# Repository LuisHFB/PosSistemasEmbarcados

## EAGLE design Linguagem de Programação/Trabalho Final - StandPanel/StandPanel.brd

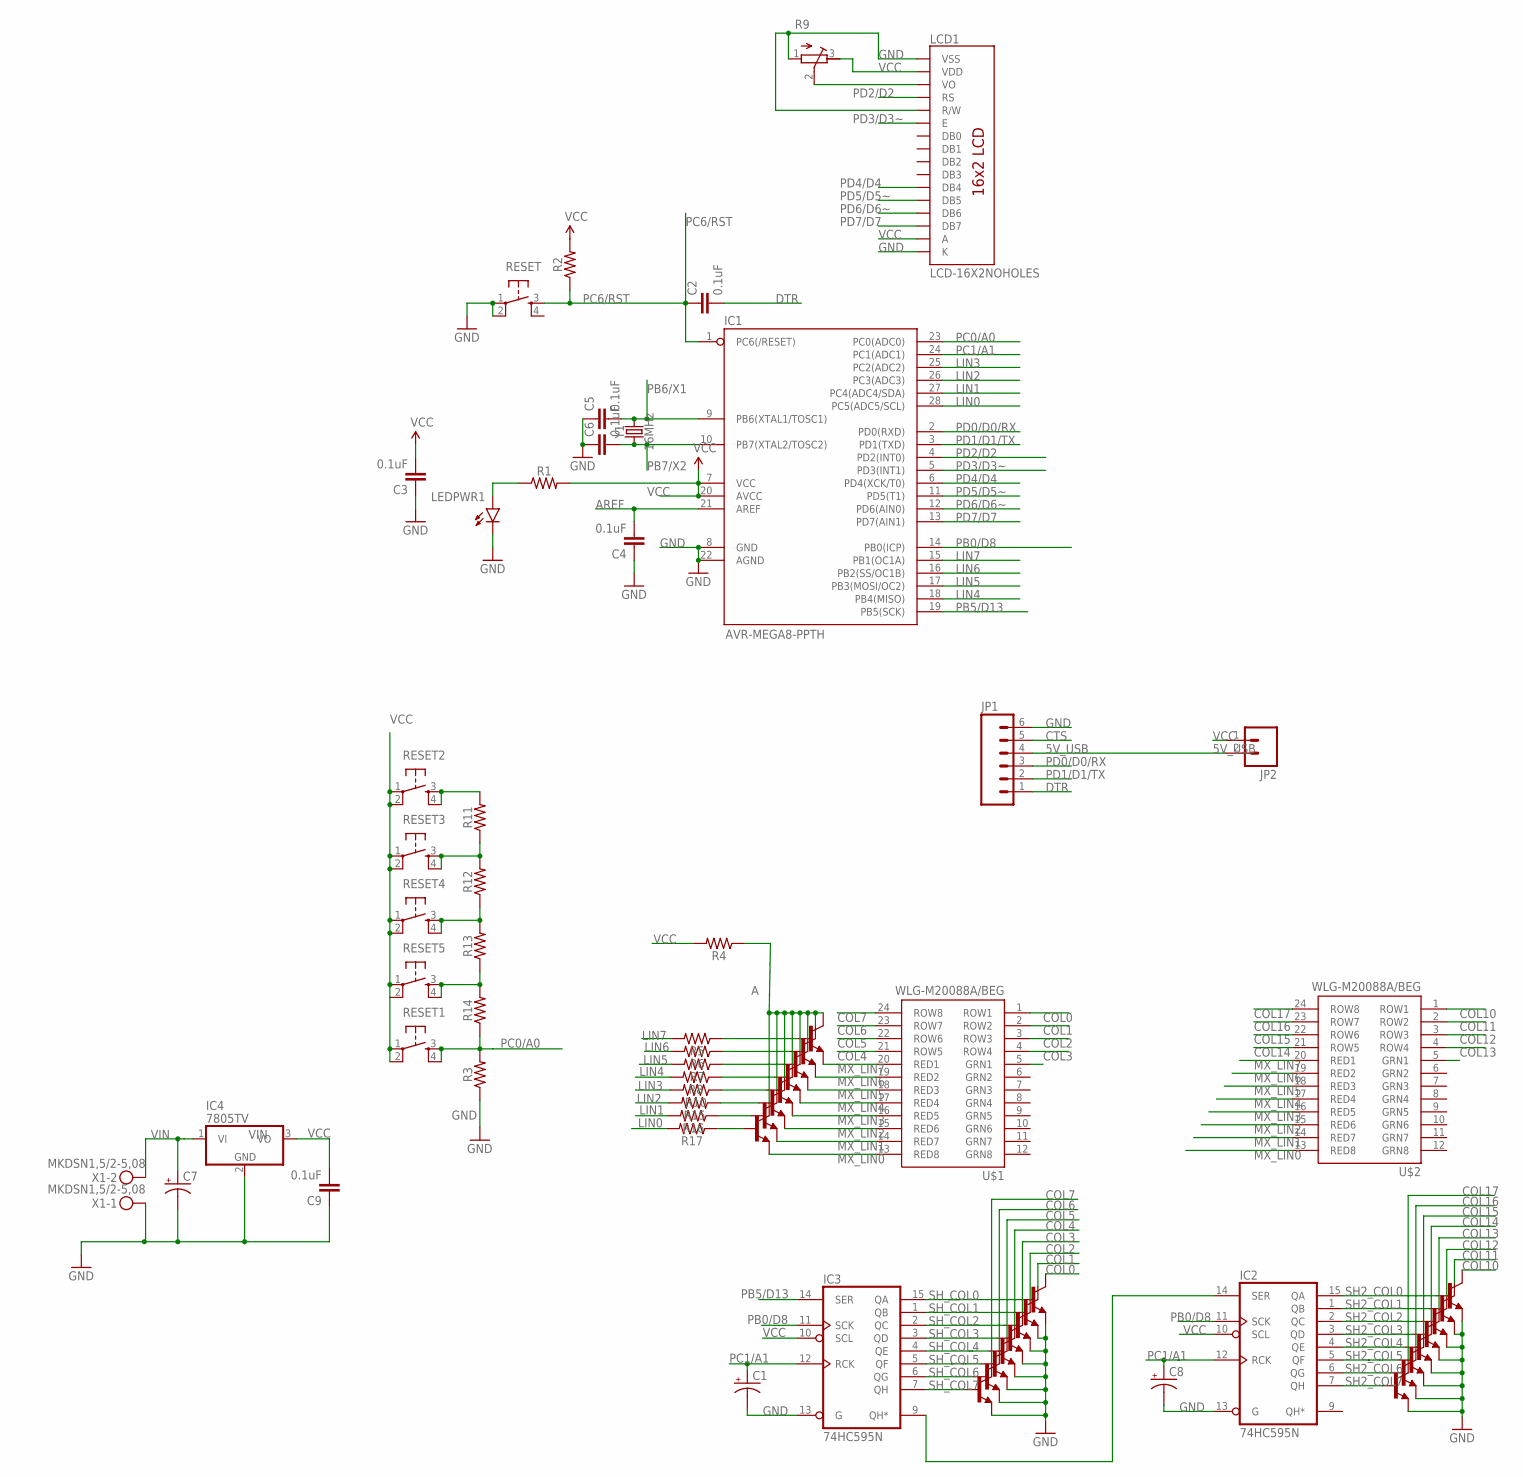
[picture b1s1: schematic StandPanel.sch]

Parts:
C1, C8: CAP_POLPTH2; CPOL-RADIAL-10UF-25V
C2, C3, C4, C5, C6, C9: 0.1uF; CAP-PTH-SMALL-KIT
C7: CAP_POLPTH1; CPOL-RADIAL-100UF-25V
IC1: AVR-MEGA8-PPTH; DIL28-3
IC2, IC3: 74HC595N; DIL16
IC4: 7805TV; TO220V
JP1: M06SIP; 1X06
JP2: M02PTH; 1X02
LCD1: LCD-16X2NOHOLES; LCD-16X2_NOHOLESNOSILK
LEDPWR1: LED5MM-KIT; LED_5MM-KIT
R1, R2, R3, R4, R5, R6, R7, R8, R10, R11, R12, R13, R14, R15, R16, R17: AXIAL-0.3-KIT
R9: R-TRIMM3296W; RTRIM3296W
RESET, RESET1, RESET2, RESET3, RESET4, RESET5: TAC_SWITCHPTH; TACTILE-PTH
T1, T3, T4, T5, T6, T7, T8, T9, T10, T11, T12, T13, T14, T15, T16, T17, T25, T26, T27, T28, T29, T30, T31, T32: BC337; TO92
U$1, U$2: WLG-M20088A/BEG; WLG-M2088A/8EG
X1: MKDSN1,5/2-5,08
Y1: 16MHz; HC49US

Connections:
5V_USB: JP1.4, JP2.2
A: R4.P$1 (1), T1.3 (C), T3.3 (C), T4.3 (C), T5.3 (C), T6.3 (C), T7.3 (C), T8.3 (C), T9.3 (C)
AREF: C4.2, IC1.21 (AREF)
COL0: T10.3 (C), U$1.1 (ROW1)
COL1: T11.3 (C), U$1.2 (ROW2)
COL2: T12.3 (C), U$1.3 (ROW3)
COL3: T13.3 (C), U$1.4 (ROW4)
COL4: T14.3 (C), U$1.21 (ROW5)
COL5: T15.3 (C), U$1.22 (ROW6)
COL6: T16.3 (C), U$1.23 (ROW7)
COL7: T17.3 (C), U$1.24 (ROW8)
COL10: T25.3 (C), U$2.1 (ROW1)
COL11: T26.3 (C), U$2.2 (ROW2)
COL12: T27.3 (C), U$2.3 (ROW3)
COL13: T28.3 (C), U$2.4 (ROW4)
COL14: T29.3 (C), U$2.21 (ROW5)
COL15: T30.3 (C), U$2.22 (ROW6)
COL16: T31.3 (C), U$2.23 (ROW7)
COL17: T32.3 (C), U$2.24 (ROW8)
CTS: JP1.5
DTR: C2.2, JP1.1
GND: C1.2 (-), C3.1, C4.1, C5.1, C6.1, C7.2 (-), C8.2 (-), C9.1, IC1.8 (GND), IC1.22 (AGND), IC2.8 (GND), IC2.13 (G), IC3.8 (GND), IC3.13 (G), IC4.2 (GND), JP1.6, LCD1.1 (VSS), LCD1.5 (R/W), LCD1.16 (K), LEDPWR1.K (C), R3.P$1 (1), R9.1 (A), RESET.1, RESET.2, T10.1 (E), T11.1 (E), T12.1 (E), T13.1 (E), T14.1 (E), T15.1 (E), T16.1 (E), T17.1 (E), T25.1 (E), T26.1 (E), T27.1 (E), T28.1 (E), T29.1 (E), T30.1 (E), T31.1 (E), T32.1 (E), X1.1
LIN0: IC1.28 (PC5(ADC5/SCL)), R17.P$2 (2)
LIN1: IC1.27 (PC4(ADC4/SDA)), R16.P$2 (2)
LIN2: IC1.26 (PC3(ADC3)), R15.P$2 (2)
LIN3: IC1.25 (PC2(ADC2)), R10.P$2 (2)
LIN4: IC1.18 (PB4(MISO)), R8.P$2 (2)
LIN5: IC1.17 (PB3(MOSI/OC2)), R7.P$2 (2)
LIN6: IC1.16 (PB2(SS/OC1B)), R6.P$2 (2)
LIN7: IC1.15 (PB1(OC1A)), R5.P$2 (2)
LIN8: T10.2 (B)
MX_LIN0: T9.1 (E), U$1.13 (RED8), U$2.13 (RED8)
MX_LIN1: T8.1 (E), U$1.14 (RED7), U$2.14 (RED7)
MX_LIN2: T7.1 (E), U$1.15 (RED6), U$2.15 (RED6)
MX_LIN3: T6.1 (E), U$1.16 (RED5), U$2.16 (RED5)
MX_LIN4: T5.1 (E), U$1.17 (RED4), U$2.17 (RED4)
MX_LIN5: T4.1 (E), U$1.18 (RED3), U$2.18 (RED3)
MX_LIN6: T3.1 (E), U$1.19 (RED2), U$2.19 (RED2)
MX_LIN7: T1.1 (E), U$1.20 (RED1), U$2.20 (RED1)
unnamed: LEDPWR1.A, R1.P$1 (1)
unnamed: R17.P$1 (1), T9.2 (B)
unnamed: R16.P$1 (1), T8.2 (B)
unnamed: LCD1.3 (VO), R9.2 (S)
unnamed: R15.P$1 (1), T7.2 (B)
unnamed: IC2.14 (SER), IC3.9 (QH*)
unnamed: R10.P$1 (1), T6.2 (B)
unnamed: R8.P$1 (1), T5.2 (B)
unnamed: R7.P$1 (1), T4.2 (B)
unnamed: R6.P$1 (1), T3.2 (B)
unnamed: R5.P$1 (1), T1.2 (B)
unnamed: R11.P$2 (2), RESET2.3, RESET2.4
unnamed: R11.P$1 (1), R12.P$2 (2), RESET3.3, RESET3.4
unnamed: R12.P$1 (1), R13.P$2 (2), RESET4.3, RESET4.4
PB0/D8: IC1.14 (PB0(ICP)), IC2.11 (SCK), IC3.11 (SCK)
PB5/D13: IC1.19 (PB5(SCK)), IC3.14 (SER)
PB6/X1: C5.2, IC1.9 (PB6(XTAL1/TOSC1)), Y1.2
PB7/X2: C6.2, IC1.10 (PB7(XTAL2/TOSC2)), Y1.1
PC0/A0: IC1.23 (PC0(ADC0)), R3.P$2 (2), R13.P$1 (1), R14.P$1 (1), R14.P$2 (2), RESET1.3, RESET1.4, RESET5.3, RESET5.4
PC1/A1: C1.1 (+), C8.1 (+), IC1.24 (PC1(ADC1)), IC2.12 (RCK), IC3.12 (RCK)
PC6/RST: C2.1, IC1.1 (PC6(/RESET)), R2.P$1 (1), RESET.3
PD0/D0/RX: IC1.2 (PD0(RXD)), JP1.3
PD1/D1/TX: IC1.3 (PD1(TXD)), JP1.2
PD2/D2: IC1.4 (PD2(INT0)), LCD1.4 (RS)
PD3/D3~: IC1.5 (PD3(INT1)), LCD1.6 (E)
PD4/D4: IC1.6 (PD4(XCK/T0)), LCD1.11 (DB4)
PD5/D5~: IC1.11 (PD5(T1)), LCD1.12 (DB5)
PD6/D6~: IC1.12 (PD6(AIN0)), LCD1.13 (DB6)
PD7/D7: IC1.13 (PD7(AIN1)), LCD1.14 (DB7)
SH2_COL0: IC2.15 (QA), T25.2 (B)
SH2_COL1: IC2.1 (QB), T26.2 (B)
SH2_COL2: IC2.2 (QC), T27.2 (B)
SH2_COL3: IC2.3 (QD), T28.2 (B)
SH2_COL4: IC2.4 (QE), T29.2 (B)
SH2_COL5: IC2.5 (QF), T30.2 (B)
SH2_COL6: IC2.6 (QG), T31.2 (B)
SH2_COL7: IC2.7 (QH), T32.2 (B)
SH_COL0: IC3.15 (QA)
SH_COL1: IC3.1 (QB), T11.2 (B)
SH_COL2: IC3.2 (QC), T12.2 (B)
SH_COL3: IC3.3 (QD), T13.2 (B)
SH_COL4: IC3.4 (QE), T14.2 (B)
SH_COL5: IC3.5 (QF), T15.2 (B)
SH_COL6: IC3.6 (QG), T16.2 (B)
SH_COL7: IC3.7 (QH), T17.2 (B)
VCC: C3.2, C9.2, IC1.7 (VCC), IC1.20 (AVCC), IC2.10 (SCL), IC2.16 (VCC), IC3.10 (SCL), IC3.16 (VCC), IC4.3 (VO), JP2.1, LCD1.2 (VDD), LCD1.15 (A), R1.P$2 (2), R2.P$2 (2), R4.P$2 (2), R9.3 (E), RESET2.1, RESET2.2, RESET3.1, RESET3.2, RESET4.1, RESET4.2, RESET5.1, RESET5.2
VCC1: RESET1.1, RESET1.2
VIN: C7.1 (+), IC4.1 (VI), X1.2

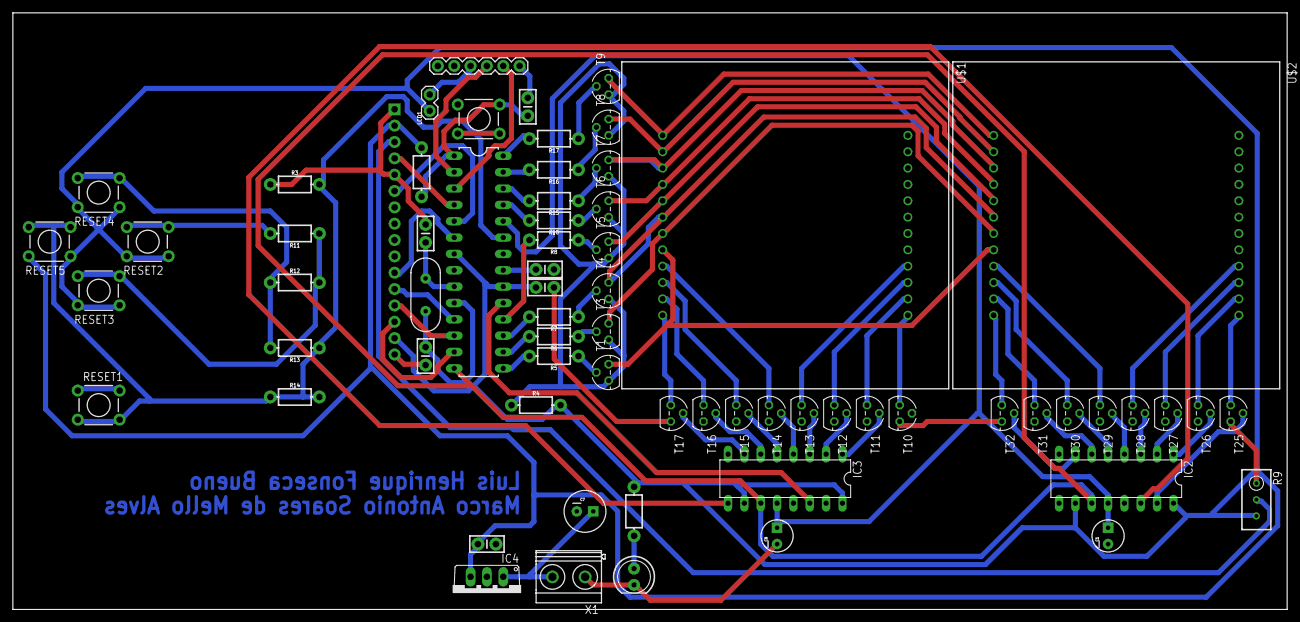
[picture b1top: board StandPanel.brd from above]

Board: 2 copper layers, 198.0 x 92.7 mm, 68 parts (0 on the bottom side), 84 nets.

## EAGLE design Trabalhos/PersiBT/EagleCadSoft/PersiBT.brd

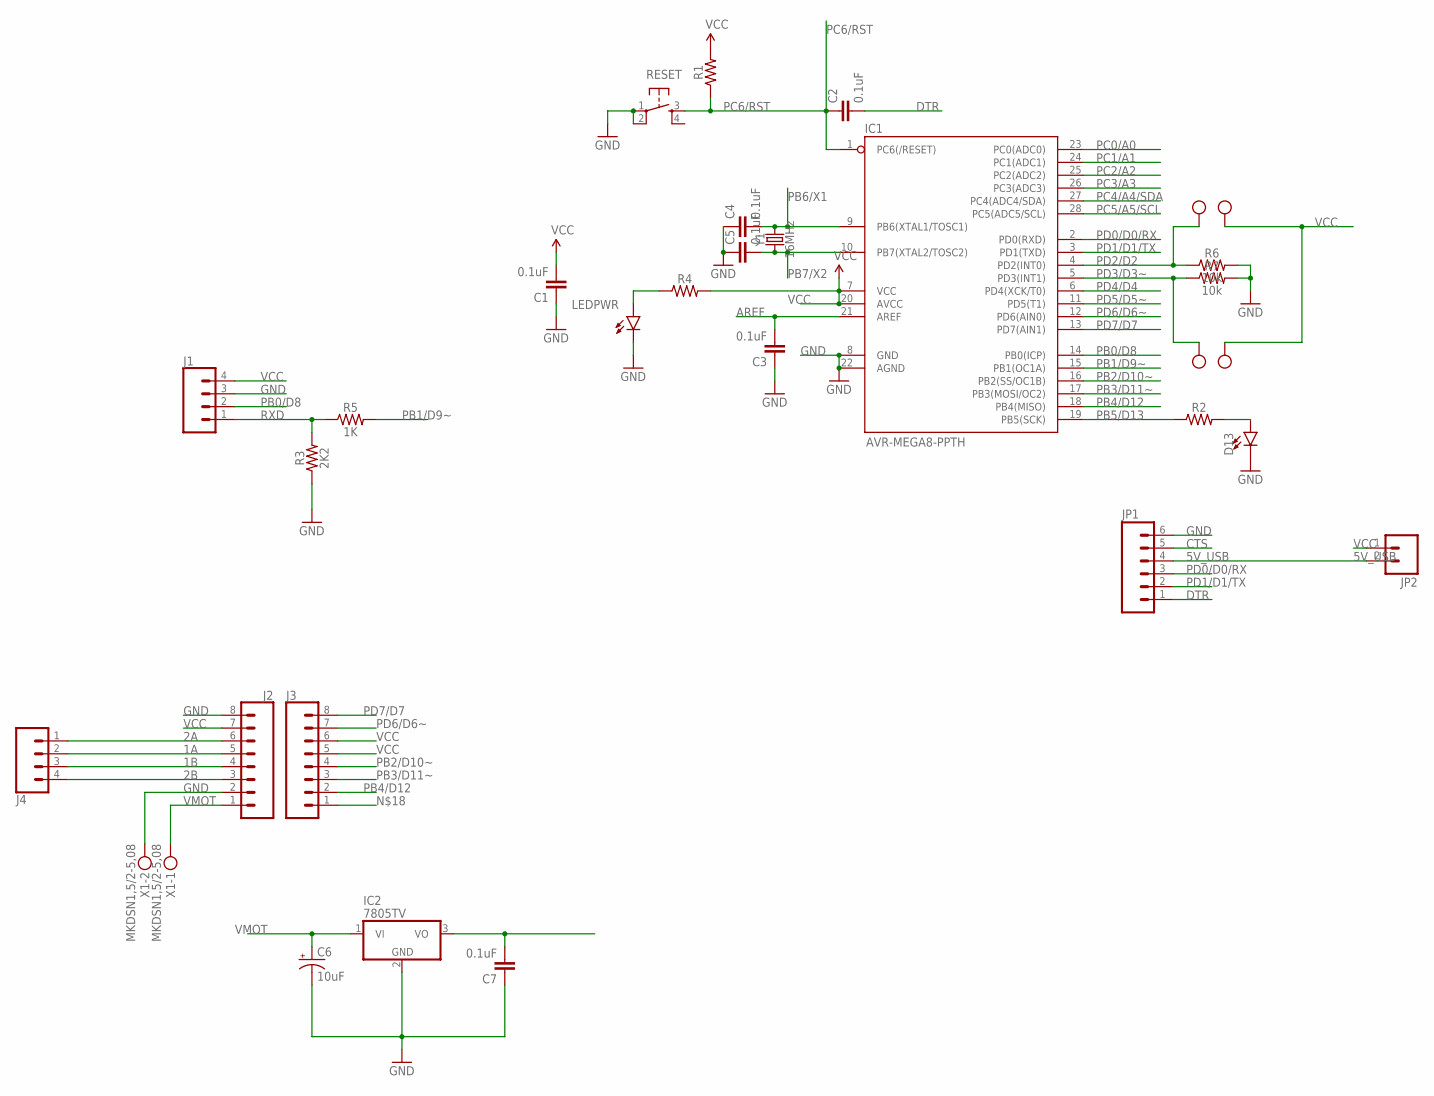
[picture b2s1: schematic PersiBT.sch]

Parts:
C1, C2, C3, C4, C5, C7: 0.1uF; CAP-PTH-SMALL-KIT
C6: 10uF; CPOL-RADIAL-2.5MM-5MM-KIT
D13: LED5MM-KIT; LED_5MM-KIT
IC1: AVR-MEGA8-PPTH; DIL28-3
IC2: 7805TV; TO220V
J1, J4: CONN_04; 1X04
J2, J3: CONN_08"; 1X08
JP1: M06SIP; 1X06
JP2: M02PTH; 1X02
LEDPWR: LED5MM-KIT; LED_5MM-KIT
R1, R2, R4: AXIAL-0.3-KIT
R3: 2K2; AXIAL-0.3-KIT
R5: 1K; AXIAL-0.3-KIT
R6, R7: 10k; AXIAL-0.3-KIT
RESET: TAC_SWITCHPTH; TACTILE-PTH
X1, X2, X3: MKDSN1,5/2-5,08
Y1: 16MHz; HC49US

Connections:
1A: J2.5, J4.2
1B: J2.4, J4.3
2A: J2.6, J4.1
2B: J2.3, J4.4
5V_USB: JP1.4, JP2.2
AREF: C3.2, IC1.21 (AREF)
CTS: JP1.5
DTR: C2.2, JP1.1
GND: C1.1, C3.1, C4.1, C5.1, C6.2 (-), C7.1, D13.K (C), IC1.8 (GND), IC1.22 (AGND), IC2.2 (GND), J1.3, J2.2, J2.8, JP1.6, LEDPWR.K (C), R3.P$1 (1), R6.P$2 (2), R7.P$2 (2), RESET.1, RESET.2, X1.2
unnamed: D13.A, R2.P$2 (2)
unnamed: LEDPWR.A, R4.P$1 (1)
PB0/D8: IC1.14 (PB0(ICP)), J1.2
PB1/D9~: IC1.15 (PB1(OC1A)), R5.P$2 (2)
PB2/D10~: IC1.16 (PB2(SS/OC1B)), J3.4
PB3/D11~: IC1.17 (PB3(MOSI/OC2)), J3.3
PB4/D12: IC1.18 (PB4(MISO)), J3.2
PB5/D13: IC1.19 (PB5(SCK)), R2.P$1 (1)
PB6/X1: C4.2, IC1.9 (PB6(XTAL1/TOSC1)), Y1.2
PB7/X2: C5.2, IC1.10 (PB7(XTAL2/TOSC2)), Y1.1
PC0/A0: IC1.23 (PC0(ADC0))
PC1/A1: IC1.24 (PC1(ADC1))
PC2/A2: IC1.25 (PC2(ADC2))
PC3/A3: IC1.26 (PC3(ADC3))
PC4/A4/SDA: IC1.27 (PC4(ADC4/SDA))
PC5/A5/SCL: IC1.28 (PC5(ADC5/SCL))
PC6/RST: C2.1, IC1.1 (PC6(/RESET)), R1.P$1 (1), RESET.3
PD0/D0/RX: IC1.2 (PD0(RXD)), JP1.3
PD1/D1/TX: IC1.3 (PD1(TXD)), JP1.2
PD2/D2: IC1.4 (PD2(INT0)), R6.P$1 (1), X2.1
PD3/D3~: IC1.5 (PD3(INT1)), R7.P$1 (1), X3.2
PD4/D4: IC1.6 (PD4(XCK/T0))
PD5/D5~: IC1.11 (PD5(T1))
PD6/D6~: IC1.12 (PD6(AIN0)), J3.7
PD7/D7: IC1.13 (PD7(AIN1)), J3.8
RXD: J1.1, R3.P$2 (2), R5.P$1 (1)
VCC: C1.2, C7.2, IC1.7 (VCC), IC1.20 (AVCC), IC2.3 (VO), J1.4, J2.7, J3.5, J3.6, JP2.1, R1.P$2 (2), R4.P$2 (2), X2.2, X3.1
VMOT: C6.1 (+), IC2.1 (VI), J2.1, X1.1

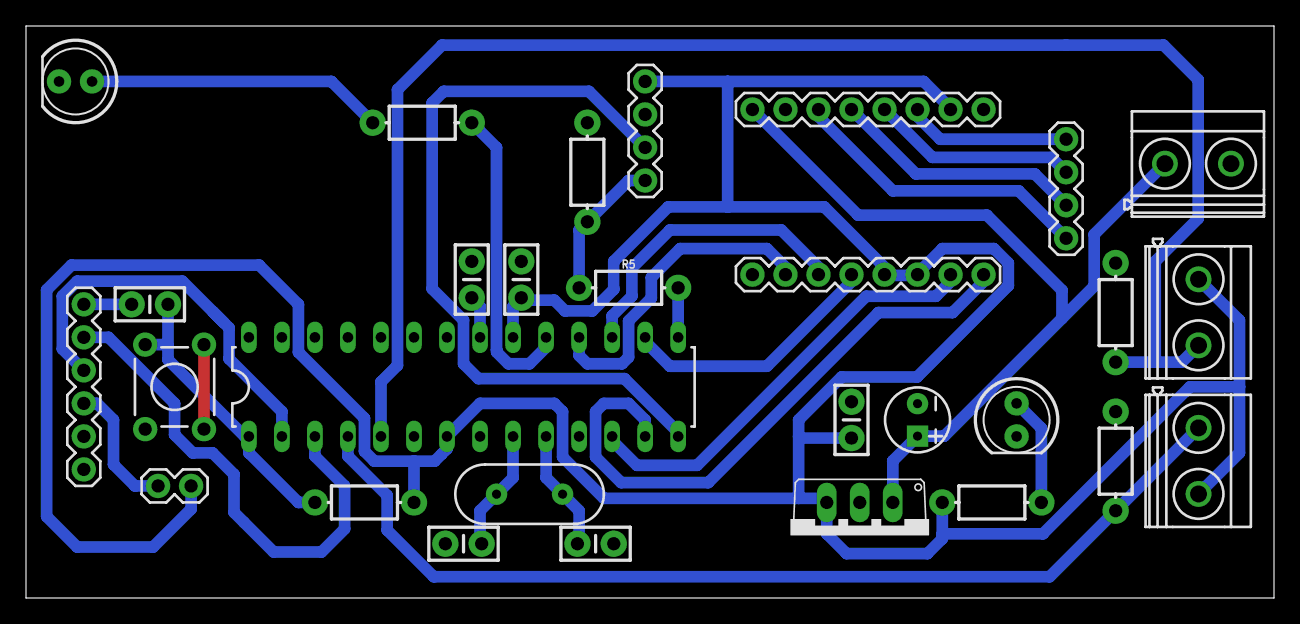
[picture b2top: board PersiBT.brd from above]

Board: 2 copper layers, 96.0 x 44.0 mm, 29 parts (0 on the bottom side), 28 nets.

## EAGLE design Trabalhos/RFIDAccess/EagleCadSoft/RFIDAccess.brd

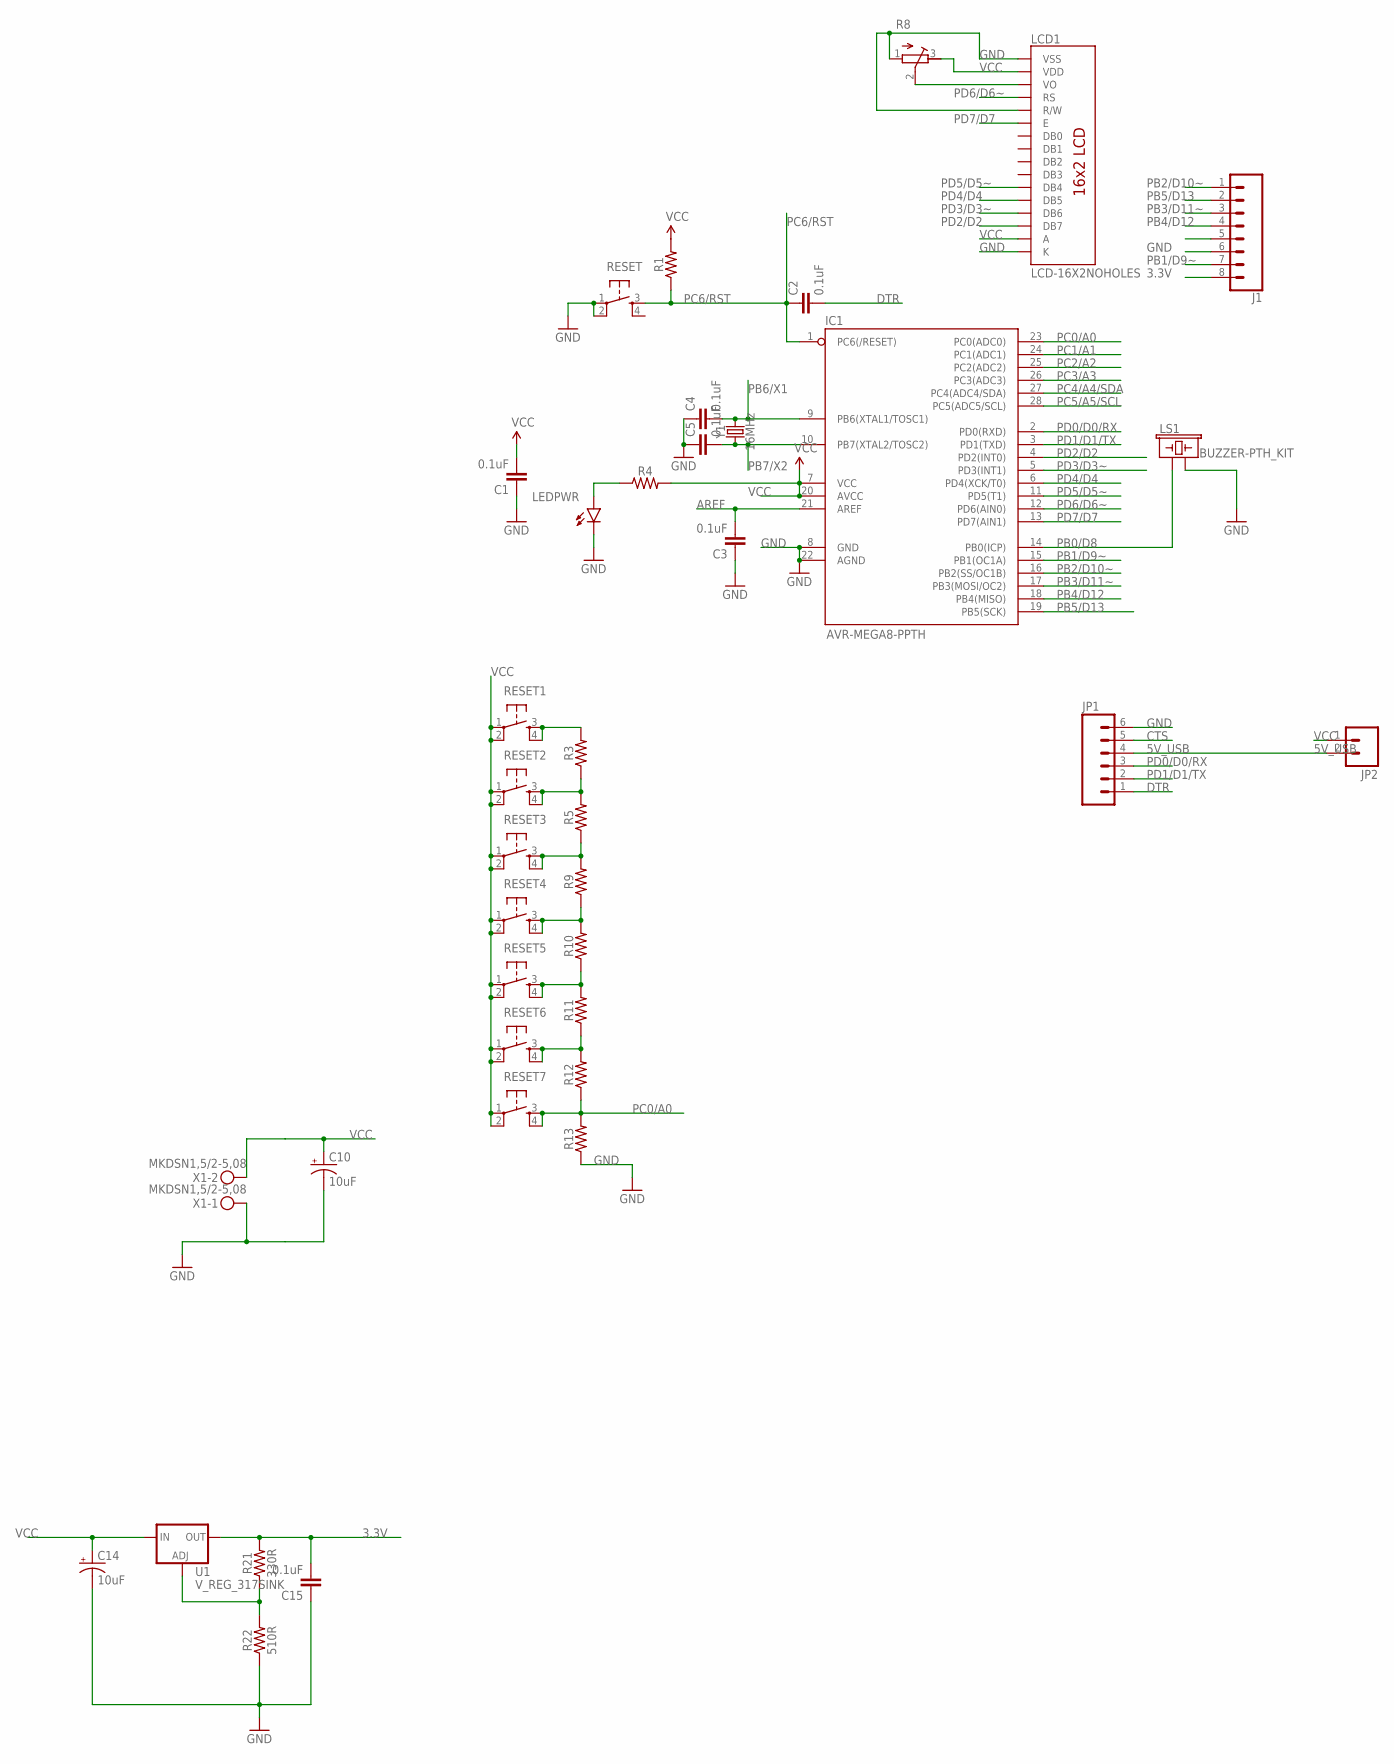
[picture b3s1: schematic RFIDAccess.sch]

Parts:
C1, C2, C3, C4, C5, C15: 0.1uF; CAP-PTH-SMALL-KIT
C10, C14: 10uF; CPOL-RADIAL-2.5MM-5MM-KIT
IC1: AVR-MEGA8-PPTH; DIL28-3
J1: CONN_08LONGPADS; 1X08_LONGPADS
JP1: M06SIP; 1X06
JP2: M02PTH; 1X02
LCD1: LCD-16X2NOHOLES; LCD-16X2_NOHOLESNOSILK
LEDPWR: LED5MM-KIT; LED_5MM-KIT
LS1: BUZZER-PTH_KIT; BUZZER-12MM-KIT
R1, R3, R4, R5, R9, R10, R11, R12, R13: AXIAL-0.3-KIT
R8: R-TRIMM3296W; RTRIM3296W
R21: 330R; AXIAL-0.3-KIT
R22: 510R; AXIAL-0.3-KIT
RESET, RESET1, RESET2, RESET3, RESET4, RESET5, RESET6, RESET7: TAC_SWITCHPTH; TACTILE-PTH
U1: V_REG_317SINK; TO220-ADJ
X1: MKDSN1,5/2-5,08
Y1: 16MHz; HC49US

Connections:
3.3V: C15.2, J1.8, R21.P$2 (2), U1.OUT
5V_USB: JP1.4, JP2.2
AREF: C3.2, IC1.21 (AREF)
CTS: JP1.5
DTR: C2.2, JP1.1
GND: C1.1, C3.1, C4.1, C5.1, C10.2 (-), C14.2 (-), C15.1, IC1.8 (GND), IC1.22 (AGND), J1.6, JP1.6, LCD1.1 (VSS), LCD1.5 (R/W), LCD1.16 (K), LEDPWR.K (C), LS1.- (2), R8.1 (A), R13.P$1 (1), R22.P$1 (1), RESET.1, RESET.2, X1.1
unnamed: LEDPWR.A, R4.P$1 (1)
unnamed: R3.P$2 (2), RESET1.3, RESET1.4
unnamed: LCD1.3 (VO), R8.2 (S)
unnamed: R3.P$1 (1), R5.P$2 (2), RESET2.3, RESET2.4
unnamed: R5.P$1 (1), R9.P$2 (2), RESET3.3, RESET3.4
unnamed: R9.P$1 (1), R10.P$2 (2), RESET4.3, RESET4.4
unnamed: R10.P$1 (1), R11.P$2 (2), RESET5.3, RESET5.4
unnamed: R11.P$1 (1), R12.P$2 (2), RESET6.3, RESET6.4
unnamed: R21.P$1 (1), R22.P$2 (2), U1.ADJ
PB0/D8: IC1.14 (PB0(ICP)), LS1.+ (1)
PB1/D9~: IC1.15 (PB1(OC1A)), J1.7
PB2/D10~: IC1.16 (PB2(SS/OC1B)), J1.1
PB3/D11~: IC1.17 (PB3(MOSI/OC2)), J1.3
PB4/D12: IC1.18 (PB4(MISO)), J1.4
PB5/D13: IC1.19 (PB5(SCK)), J1.2
PB6/X1: C4.2, IC1.9 (PB6(XTAL1/TOSC1)), Y1.2
PB7/X2: C5.2, IC1.10 (PB7(XTAL2/TOSC2)), Y1.1
PC0/A0: IC1.23 (PC0(ADC0)), R12.P$1 (1), R13.P$2 (2), RESET7.3, RESET7.4
PC1/A1: IC1.24 (PC1(ADC1))
PC2/A2: IC1.25 (PC2(ADC2))
PC3/A3: IC1.26 (PC3(ADC3))
PC4/A4/SDA: IC1.27 (PC4(ADC4/SDA))
PC5/A5/SCL: IC1.28 (PC5(ADC5/SCL))
PC6/RST: C2.1, IC1.1 (PC6(/RESET)), R1.P$1 (1), RESET.3
PD0/D0/RX: IC1.2 (PD0(RXD)), JP1.3
PD1/D1/TX: IC1.3 (PD1(TXD)), JP1.2
PD2/D2: IC1.4 (PD2(INT0)), LCD1.14 (DB7)
PD3/D3~: IC1.5 (PD3(INT1)), LCD1.13 (DB6)
PD4/D4: IC1.6 (PD4(XCK/T0)), LCD1.12 (DB5)
PD5/D5~: IC1.11 (PD5(T1)), LCD1.11 (DB4)
PD6/D6~: IC1.12 (PD6(AIN0)), LCD1.4 (RS)
PD7/D7: IC1.13 (PD7(AIN1)), LCD1.6 (E)
VCC: C1.2, C10.1 (+), C14.1 (+), IC1.7 (VCC), IC1.20 (AVCC), JP2.1, LCD1.2 (VDD), LCD1.15 (A), R1.P$2 (2), R4.P$2 (2), R8.3 (E), RESET1.1, RESET1.2, RESET2.1, RESET2.2, RESET3.1, RESET3.2, RESET4.1, RESET4.2, RESET5.1, RESET5.2, RESET6.1, RESET6.2, RESET7.1, RESET7.2, U1.IN, X1.2

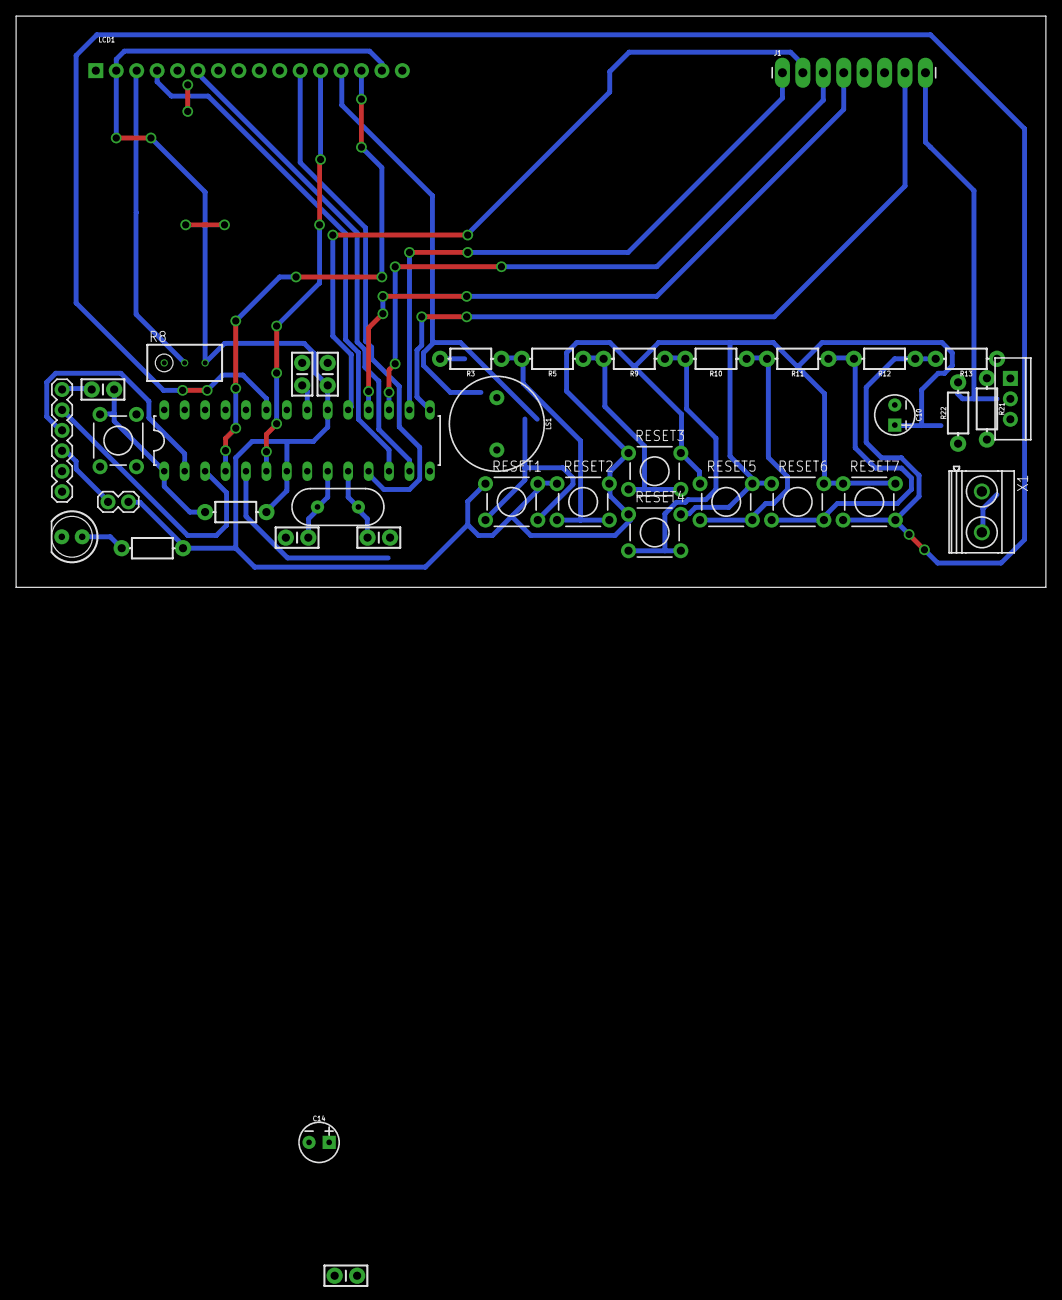
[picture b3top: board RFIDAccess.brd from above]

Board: 2 copper layers, 128.0 x 71.0 mm, 38 parts (0 on the bottom side), 33 nets.

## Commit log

2018-09-20 19_09_2018
2018-09-24 24_09_2018(2)
2018-09-25 25_09_2018
2018-09-26 26_09_2018
2018-09-27 27_09_2018
2018-09-28 28/09/2018_(2)
2018-09-28 29_09_2018(3)
2018-09-28 28_09_2018_(4)
2018-10-01 30_09_2018
2018-10-05 04_10_2018
2018-10-06 05_10_2018
2018-10-09 09_10_2018

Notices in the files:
parts and their libraries:
SparkFun-Resistors: Licensing: Creative Commons ShareAlike 4.0 International - https://creativecommons.org/licenses/by-sa/4.0
SparkFun-DigitalIC: Licensing: CC v3.0 Share-Alike You are welcome to use this library for commercial purposes.
